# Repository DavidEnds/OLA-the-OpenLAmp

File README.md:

# OLA-the-OpenLAmp
Open source boards for a led cube lamp

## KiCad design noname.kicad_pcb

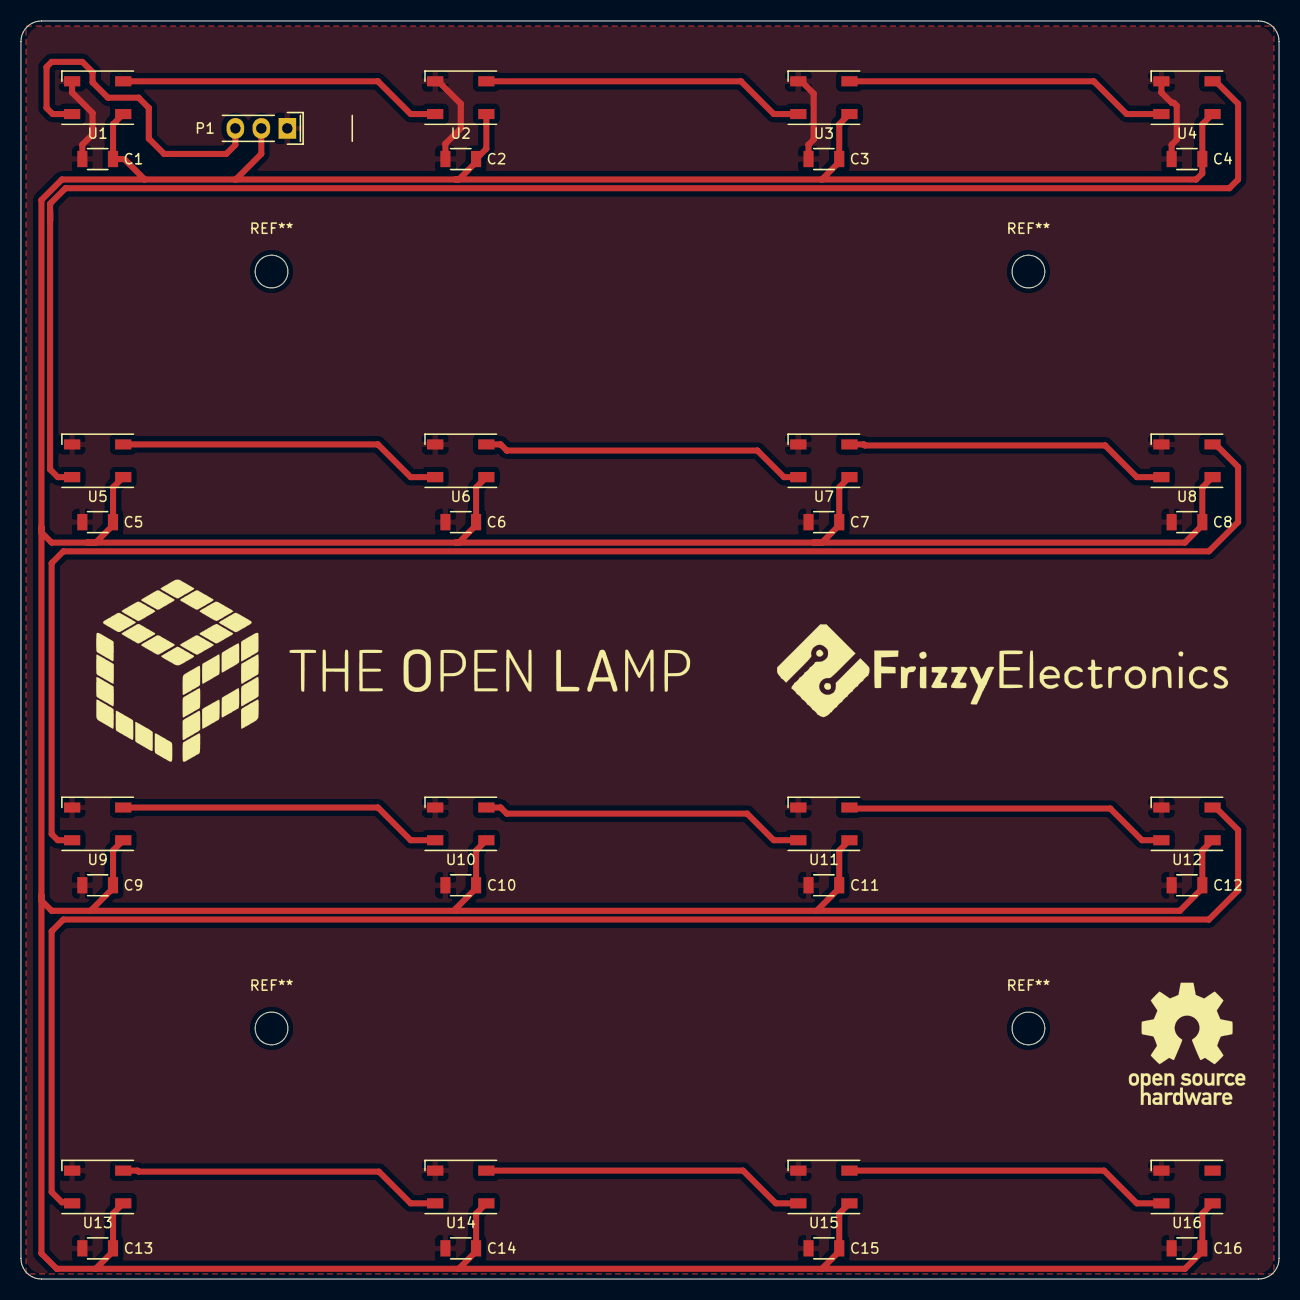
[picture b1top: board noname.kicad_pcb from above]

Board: 2 copper layers, 123.0 x 123.0 mm, 33 parts (1 on the bottom side), 18 nets.

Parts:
C1, C2, C3, C4, C5, C6, C7, C8, C9, C10, C11, C12, C13, C14, C15, C16: 100n; C_1206
P1: CONN_01X03; Pin_Header_Straight_1x03
U1, U2, U3, U4, U5, U6, U7, U8, U9, U10, U11, U12, U13, U14, U15, U16: WS2812B; LED_WS2812B-PLCC4

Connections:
+5V: C1.2, C2.2, C3.2, C4.2, C5.2, C6.2, C7.2, C8.2, C9.2, C10.2, C11.2, C12.2, C13.2, C14.2, C15.2, C16.2, P1.2, U1.1, U2.1, U3.1, U4.1, U5.1, U6.1, U7.1, U8.1, U9.1, U10.1, U11.1, U12.1, U13.1, U14.1, U15.1, U16.1
GND: C1.1, C2.1, C3.1, C4.1, C5.1, C6.1, C7.1, C8.1, C9.1, C10.1, C11.1, C12.1, C13.1, C14.1, C15.1, C16.1, P1.1, U1.3, U2.3, U3.3, U4.3, U5.3, U6.3, U7.3, U8.3, U9.3, U10.3, U11.3, U12.3, U13.3, U14.3, U15.3, U16.3
unnamed: P1.3, U1.4
unnamed: U1.2, U2.4
unnamed: U2.2, U3.4
unnamed: U3.2, U4.4
unnamed: U4.2, U5.4
unnamed: U5.2, U6.4
unnamed: U6.2, U7.4
unnamed: U7.2, U8.4
unnamed: U8.2, U9.4
unnamed: U10.2, U11.4
unnamed: U9.2, U10.4
unnamed: U11.2, U12.4
unnamed: U12.2, U13.4
unnamed: U13.2, U14.4
unnamed: U14.2, U15.4
unnamed: U15.2, U16.4

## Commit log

2017-03-15 Add files via upload
    the OpenLAmp
